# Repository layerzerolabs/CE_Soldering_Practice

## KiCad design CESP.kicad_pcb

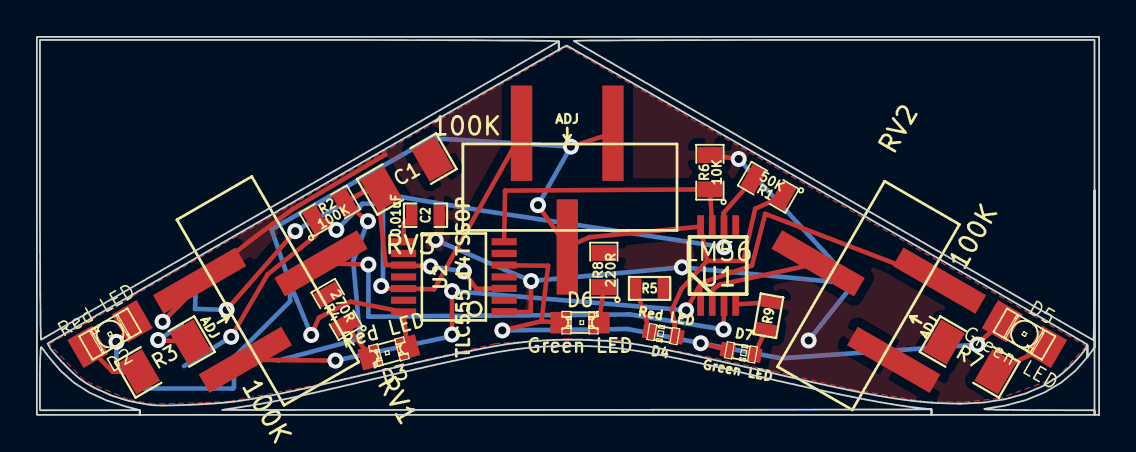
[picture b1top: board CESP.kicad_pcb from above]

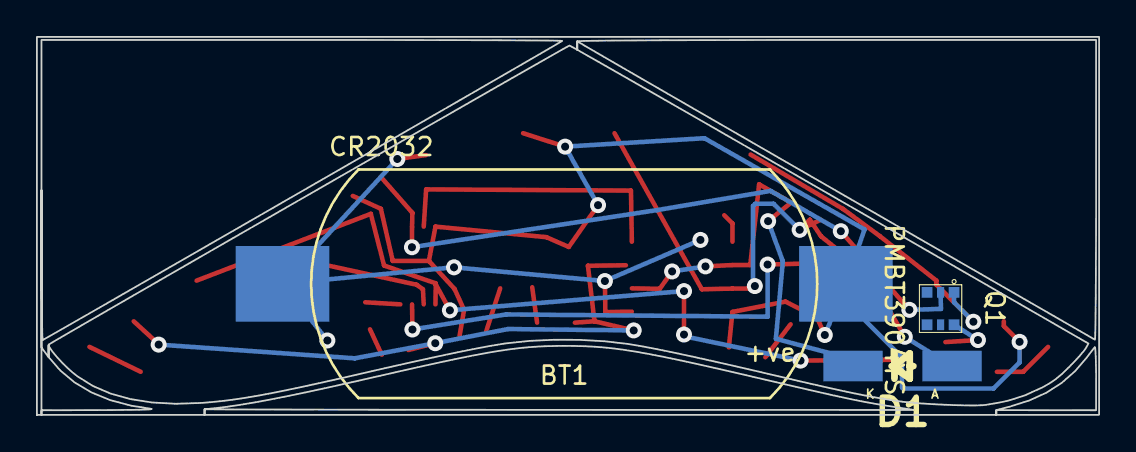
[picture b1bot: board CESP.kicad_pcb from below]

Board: 2 copper layers, 59.0 x 21.0 mm, 25 parts (3 on the bottom side), 18 nets.

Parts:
BT1: CR2032; CR2032_Batt_Holder
C1: 10uF; SM1206
C2: 0.01uF; SM0603_Capa
D1: FDLL4148; Diode-MiniMELF_Handsoldering
D2: Red LED; LED-1206
D3: Red LED; LED-0805
D4: Red LED; LED-0603
D5: Green LED; LED-1206
D6: Green LED; LED-0805
D7: Green LED; LED-0603
Q1: PMBT3904YS; SOT363
R1: 50K; SM0805
R2: 100K; SM0805
R3: 270R; SM1206
R4: 270R; SM0805
R5: 270R; SM0603
R6: 10K; SM0805
R7: 220R; SM1206
R8: 220R; SM0805
R9: 220R; SM0603
RV1, RV2, RV3: 100K; TRIM_SMD_SIDE_ADJ
U1: LM56; MSOP_8
U2: TLC555_14TSSOP; SSOP-14

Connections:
GND: BT1.2, C1.2, C2.2, Q1.1, R6.2, R7.2, R8.2, R9.2, RV1.3, RV2.3, U1.4, U2.1
unnamed: C1.1, D1.2, R2.2, U2.3, U2.10
unnamed: C2.1, U2.8
unnamed: D1.1, R2.1, RV3.1, U2.12
unnamed: D2.2, R3.1
unnamed: D3.2, R4.1
unnamed: D4.2, R5.1
unnamed: D5.1, D6.1, D7.1, U2.5
unnamed: D5.2, R7.1
unnamed: D6.2, R8.1
unnamed: D7.2, R9.1
unnamed: Q1.2, R1.2, U1.6
unnamed: Q1.6, R3.2
unnamed: R6.1, U1.7, U2.7
unnamed: RV1.1, RV2.1, U1.1
unnamed: RV1.2, U1.3
unnamed: RV2.2, U1.2
VCC: BT1.1, D2.1, D3.1, D4.1, R1.1, RV3.2, RV3.3, U1.8, U2.14

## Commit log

2014-02-01 my soldering practice board complete with schematic
